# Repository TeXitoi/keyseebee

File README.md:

# KeySeeBee

KeySeeBee is a split ergo keyboard. It is only 2 PCB (so the name)
with (almost) only SMD components on it. It's only a keyboard, no LED,
no display, nothing more than keys and USB.

The firmware is [Keyberon](https://github.com/TeXitoi/keyberon), a
pure rust firmware.

## Features

 * 44 keys, using Cherry MX or Kailh choc switches, only 1U keycaps.
 * USB-C connector on the 2 sides.
 * TRRS cable for connecting the 2 halves (for power and UART communication between the 2 halves).
 * 2 STM32F072 MCU, with hardware USB DFU bootloader and crystal less USB;
 * Only onboard SMD component (except for the switches and TRRS
   connector).
 * [Plate files](cad/) (optional).

## Inspiration

 * [Plaid](https://github.com/hsgw/plaid) for "show the components"
 * [GergoPlex](https://www.gboards.ca/product/gergoplex) for "just a keyboard" and "only a PCB with SMD components"
 * [Lily58](https://github.com/kata0510/Lily58) for the thumb cluster
 * [Kyria](https://blog.splitkb.com/blog/introducing-the-kyria) for
   "don't be affraid of pinky stagger"

## Gallery

### v0.1, build by TeXitoi

### v0.1, build by TeXitoi, Gateron silent clear (MX footprint), 3D printed plate

### v0.2, build by eropleco, with 1.2mm anodized aluminium plate

### v0.3, build by TeXitoi, Gateron silent clear, 3D printed fat plate

## Bill Of Materials

Price is for 5 keyboards including shipping.

|Item                                                                      |Package|Qty|Remarks                                |Price |
|--------------------------------------------------------------------------|-------|--:|---------------------------------------|-----:|
|[Left PCB](pcb/gerbers/)                                                  |       |  1|Ordered at [JLCPCB](https://jlcpcb.com)|      |
|[Right PCB](pcb/gerbers/)                                                 |       |  1|Ordered at [JLCPCB](https://jlcpcb.com)|33.14€|
|[USB-C connector](https://www.aliexpress.com/item/33004501788.html)       |16 pins|  2|                                       | 1.44€|
|[1N4148WS](https://www.aliexpress.com/item/32774043752.html)              |SOD-323| 44|Price is for 1000                      | 2.82€|
|[PJ320A TRRS connector](https://www.aliexpress.com/item/4000661212458.html)|      |  2|                                       | 1.01€|
|[STM32F072CBT6 MCU](https://www.aliexpress.com/item/1005002841528809.html)|LQFP-48|  2|STM32F072C8T6 would also work          | 9.65€|
|[XC6206P332MR regulator](https://www.aliexpress.com/item/33015891307.html)|SOT-23 |  2|Price is for 50                        | 1.93€|
|[SMD switch](https://www.aliexpress.com/item/4000546059630.html)          | 3×6mm |  4|Price is for 100                       | 1.35€|
|[5.1kΩ resistor](https://www.aliexpress.com/item/32865947306.html)        | 0805  |  6|Price is for 100                       |      |
|[1µF capacitor](https://www.aliexpress.com/item/32964553793.html)         | 0805  |  4|Price is for 100                       |      |
|[100nF capacitor](https://www.aliexpress.com/item/32964553793.html)       | 0805  | 10|Price is for 100                       | 3.46€|
|[Bumpers](https://www.aliexpress.com/item/32289191938.html)               | 5×2mm | 10|Price is for 100                       | 1.75€|
|[Cherry MX compatible](https://www.aliexpress.com/item/32836368723.html) or [Kailh Choc](https://www.aliexpress.com/item/1005005883472162.html) switch|5 pins (PCB mount)|44| | |
|1U keycap compatible with the chosen switches                             |       | 44|                                       |      |
|[TRRS cable](https://www.aliexpress.com/item/1005003677396291.html)       |Jack 3.5mm| 1|4 contacts needed                    |      |
|[USB-C cable](https://www.aliexpress.com/item/1005002811739151.html)      |       |  1|USB-2 is enough                        |      |

About 60€ without switches, keycaps and cables for 5 keyboards
(12€/keyboard).

## Compiling and flashing

Install the complete toolchain and utils:

```shell
curl https://sh.rustup.rs -sSf | sh
rustup target add thumbv6m-none-eabi
rustup component add llvm-tools-preview
cargo install cargo-binutils
sudo apt-get install dfu-util
```

Compile:

```shell
cd firmware
cargo objcopy --bin keyseebee --release -- -O binary keyseebee.bin
```

To flash using dfu-util, launch it with:
```shell
dfu-util -w -d 0483:df11 -a 0 -s 0x08000000:leave -D keyseebee.bin
```
Then, put the board in dfu mode by pressing BOOT, pressing and releasing
RESET and releasing BOOT. The upload should began as soon as the
computer detect the board in dfu mode.

The first time, if the write fail, your flash might be protected. To
unprotect:

```shell
dfu-util -d 0483:df11 -a 0 -s 0x08000000:force:unprotect -D keyseebee.bin
```

Ideally both sides needs to be flashed, but for changes that only affect the layout it's strictly not needed as the side connected with the USB cable will determine the layout. In fact, you can have different layouts stored on each half, meaning you can switch back and forth between two layouts by moving the USB cable between the two halves.

## What's the layout

Here is the [empty keyboard-layout-editor](http://www.keyboard-layout-editor.com/##@_name=Keyseebee%3B&@_y:0.35&x:3&sm=cherry&a:7&f:4%3B&=&_x:9%3B&=%3B&@_y:-0.85&x:2%3B&=&_x:1%3B&=&_x:7%3B&=&_x:1%3B&=%3B&@_y:-0.875&x:5%3B&=&_x:5%3B&=%3B&@_y:-0.625&x:1%3B&=&_x:13%3B&=%3B&@_y:-0.8500000000000001%3B&=&_x:15&f:3%3B&=%3B&@_y:-0.8&x:3&f:4%3B&=&_x:9%3B&=%3B&@_y:-0.8500000000000001&x:2%3B&=&_x:1%3B&=&_x:7%3B&=&_x:1%3B&=%3B&@_y:-0.875&x:5%3B&=&_x:5%3B&=%3B&@_y:-0.625&x:1%3B&=&_x:13%3B&=%3B&@_y:-0.8500000000000001%3B&=&_x:15&f:3%3B&=%3B&@_y:-0.7999999999999998&x:3&f:4%3B&=&_x:9%3B&=%3B&@_y:-0.8500000000000001&x:2%3B&=&_x:1%3B&=&_x:7%3B&=&_x:1%3B&=%3B&@_y:-0.875&x:5%3B&=&_x:5%3B&=%3B&@_y:-0.625&x:1%3B&=&_x:13%3B&=%3B&@_y:-0.8500000000000001%3B&=&_x:15&f:3%3B&=%3B&@_y:-0.6499999999999999&x:2.5&f:4%3B&=&_x:10%3B&=%3B&@_rx:4&ry:8.175&y:-4.675&x:-0.5%3B&=%3B&@_y:-0.875&x:0.5%3B&=%3B&@_rx:13&y:-4.675&x:-0.5%3B&=%3B&@_y:-0.875&x:-1.5%3B&=%3B&@_r:30&rx:4&y:-4.825&x:-0.5&f:3%3B&=%3B&@_r:-30&rx:13&y:-4.825&x:-0.5%3B&=) describing the layout.

I use the [ergol layout](https://ergol.org), so this is [the main layer](http://www.keyboard-layout-editor.com/##@_name=keyseebee%20Ergo-l%3B&@_y:0.35&x:3&sm=cherry&f:4%3B&=%0A%0A%C5%93%0A%3E%0A%0A%0AO&_x:9%3B&=%0A%0A%2F_%0A*%0A%0A%0AD%3B&@_y:-0.8500000000000001&x:2%3B&=%0A%0A%C3%A7%0A%3C%0A%0A%0AC&_x:1%3B&=%0A%0A%C3%B4%0A$%0A%0A%0AP&_x:7%3B&=%0A%0A%C2%B5%0A%2F&%0A%0A%0AM&_x:1%3B&=!%0A%E2%91%A0%0A%C2%A8%0A'%3B&@_y:-0.875&x:5%3B&=%0A%0A%0A%25%0A%0A%0AW&_x:5%3B&=%0A%0A%0A%2F@%0A%0A%0AJ%3B&@_y:-0.625&x:1%3B&=%0A%0A%C3%A2%0A%5E%0A%0A%0AQ&_x:13%3B&=%0A%0A%C3%BB%0A%60%0A%0A%0AY%3B&@_y:-0.8500000000000001&a:6%3B&=Tab&_x:15&a:4&f:3%3B&=%7B%0A%5B%3B&@_y:-0.7999999999999998&x:3&f:4%3B&=%0A%0A%C3%A8%0A%29%0A%0A%0AE&_x:9%3B&=%0A%0A%C3%AE%0A-%0A%0A%0AT%3B&@_y:-0.8500000000000001&x:2%3B&=%0A%0A%C3%A9%0A%28%0A%0A%0AS&_x:1%3B&=%0A%0A%C3%AA%0A%7D%0A%0A%0AN&_x:7%3B&=%0A%0A%29%0A+%0A%0A%0AR&_x:1%3B&=%0A%0A%C3%AF%0A%2F%2F%0A%0A%0AI%3B&@_y:-0.875&x:5%3B&=%0A%0A%C3%B1%0A%2F=%0A%0A%0AF&_x:5%3B&=%0A%0A%28%0A%5C%0A%0A%0AL%3B&@_y:-0.625&x:1%3B&=%0A%0A%C3%A0%0A%7B%0A%0A%0AA&_x:13%3B&=%0A%0A%C3%B9%0A%22%0A%0A%0AU%3B&@_y:-0.8500000000000001%3B&=%7D%0A%5D&_x:15&f:3%3B&=%22%0A'%3B&@_y:-0.7999999999999998&x:3&f:4%3B&=%3F%0A-%0A%E2%80%91%0A%5D&_x:9%3B&=%0A%0A%CE%B1%0A%2F%3B%0A%0A%0AG%3B&@_y:-0.8500000000000001&x:2%3B&=%0A%0A%C3%9F%0A%5B%0A%0A%0AX&_x:1%3B&=%0A%0A%E2%80%93%0A%2F_%0A%0A%0AV&_x:7%3B&=%0A%0A%0A!%0A%0A%0AH&_x:1%3B&=%2F%3B%0A,%0A%C2%B7%0A%2F:%3B&@_y:-0.875&x:5%3B&=%0A%0A%E2%80%94%0A%23%0A%0A%0AB&_x:5%3B&=%2F:%0A.%0A%E2%80%A6%0A%7C%3B&@_y:-0.625&x:1%3B&=%0A%0A%C3%A6%0A~%0A%0A%0AZ&_x:13%3B&=%0A%0A%C5%AD%0A%3F%0A%0A%0AK%3B&@_y:-0.8500000000000001%3B&=+%0A%2F=&_x:15&f:3%3B&=%7C%0A%5C%3B&@_y:-0.6500000000000004&x:2.5&a:6&f:4%3B&=GUI&_x:10%3B&=%E2%87%A7%20+%20AltGr%3B&@_rx:4&ry:8.175&y:-4.675000000000001&x:-0.5%3B&=Alt%3B&@_y:-0.875&x:0.5&a:0%3B&=nbsp%0A%E2%90%A3%0A%E2%80%99%0A%E2%90%A3%0Alayer%201%3B&@_rx:13&y:-4.675000000000001&x:-0.5&a:6%3B&=AltGr%3B&@_y:-0.875&x:-1.5&a:7%3B&=Layer%202%3B&@_r:30&rx:4&y:-4.825000000000001&x:-0.5&a:6&f:3%3B&=Ctrl%3B&@_r:-30&rx:13&y:-4.825000000000001&x:-0.5%3B&=%E2%87%A7) when I type.

The [layer 1](http://www.keyboard-layout-editor.com/##@_name=Keyseebee%20layer%201%3B&@_y:0.35&x:3&sm=cherry&a:7&f:4%3B&=Scroll%20Lock&_x:9%3B&=Del.%3B&@_y:-0.85&x:2%3B&=Caps%20Lock&_x:1%3B&=Print%20Scr.&_x:7%3B&=%E2%8C%AB&_x:1%3B&=Insert%3B&@_y:-0.875&x:5%3B&=%E2%87%A7%20+%20Tab&_x:5%3B&=%3B&@_y:-0.625&x:1%3B&=Break&_x:13%3B&=%3B&@_y:-0.8500000000000001%3B&=&_x:15&f:3%3B&=%3B&@_y:-0.8&x:3&f:4%3B&=Esc.%0A%0A%0A%0ACtrl&_x:9%3B&=%E2%96%BC%3B&@_y:-0.8500000000000001&x:2%3B&=Alt&_x:1%3B&=%E2%87%A7&_x:7%3B&=%E2%97%84&_x:1%3B&=%E2%96%B2%3B&@_y:-0.875&x:5%3B&=Tab&_x:5%3B&=%3B&@_y:-0.625&x:1%3B&=GUI&_x:13%3B&=%E2%96%BA%3B&@_y:-0.8500000000000001%3B&=&_x:15&f:3%3B&=%3B&@_y:-0.7999999999999998&x:3&f:4%3B&=Copy&_x:9%3B&=%E2%87%9F%3B&@_y:-0.8500000000000001&x:2%3B&=Cut&_x:1%3B&=Paste&_x:7%3B&=%E2%87%B1&_x:1%3B&=%E2%87%9E%3B&@_y:-0.875&x:5%3B&=&_x:5%3B&=%E2%8F%8E%3B&@_y:-0.625&x:1%3B&=Undo&_x:13%3B&=%E2%87%B2%3B&@_y:-0.8500000000000001%3B&=&_x:15&f:3%3B&=%3B&@_y:-0.6499999999999999&x:2.5&f:4%3B&=&_x:10%3B&=%3B&@_rx:4&ry:8.175&y:-4.675&x:-0.5%3B&=%3B&@_y:-0.875&x:0.5&g:true%3B&=%3B&@_rx:13&y:-4.675&x:-0.5&g:false%3B&=%3B&@_y:-0.875&x:-1.5%3B&=Layer%203%3B&@_r:30&rx:4&y:-4.825&x:-0.5&f:3%3B&=%3B&@_r:-30&rx:13&y:-4.825&x:-0.5&f:4%3B&=) is activated by holding `space`.

The [layer 2](http://www.keyboard-layout-editor.com/##@_name=keyseebee%20layer%203%3B&@_y:0.35&x:3&sm=cherry&a:7&f:4%3B&=%C2%BB&_x:9%3B&=%3B&@_y:-0.85&x:2%3B&=%C2%AB&_x:1%3B&=nbsp&_x:7%3B&=&_x:1%3B&=%E2%91%A0%3B&@_y:-0.875&x:5%3B&=&_x:5%3B&=%3B&@_y:-0.625&x:1%3B&=%E2%82%AC&_x:13%3B&=%3B&@_y:-0.8500000000000001%3B&=&_x:15&f:3%3B&=%3B&@_y:-0.8&x:3&f:4%3B&=3&_x:9%3B&=8%3B&@_y:-0.8500000000000001&x:2%3B&=2&_x:1%3B&=4&_x:7%3B&=7&_x:1%3B&=9%3B&@_y:-0.875&x:5%3B&=5&_x:5%3B&=6%3B&@_y:-0.625&x:1%3B&=1&_x:13%3B&=0%3B&@_y:-0.8500000000000001%3B&=%60&_x:15&f:3%3B&=%2F%2F%3B&@_y:-0.7999999999999998&x:3&f:4%3B&=%2F:&_x:9%3B&=-%3B&@_y:-0.8500000000000001&x:2%3B&=nbsp&_x:1%3B&=,&_x:7%3B&=+&_x:1%3B&=%2F%2F%3B&@_y:-0.875&x:5%3B&=%2F=&_x:5%3B&=.%3B&@_y:-0.625&x:1%3B&=&_x:13%3B&=*%3B&@_y:-0.8500000000000001%3B&=&_x:15&f:3%3B&=%3B&@_y:-0.6499999999999999&x:2.5&a:6&f:4%3B&=GUI&_x:10&a:7%3B&=%3B&@_rx:4&ry:8.175&y:-4.675&x:-0.5&a:6%3B&=Alt%3B&@_y:-0.875&x:0.5&a:7%3B&=Ctrl+%E2%90%A3%3B&@_rx:13&y:-4.675&x:-0.5%3B&=AltGr%3B&@_y:-0.875&x:-1.5&g:true%3B&=%3B&@_r:30&rx:4&y:-4.825&x:-0.5&g:false&a:6&f:3%3B&=Ctrl%3B&@_r:-30&rx:13&y:-4.825&x:-0.5%3B&=%E2%87%A7) is activated by holding `Layer 2`.

The [layer 3](http://www.keyboard-layout-editor.com/##@_name=Keyseebee%20layer%203%3B&@_y:0.35&x:3&sm=cherry&a:7&f:4%3B&=F3&_x:9%3B&=F8%3B&@_y:-0.85&x:2%3B&=F2&_x:1%3B&=F4&_x:7%3B&=F7&_x:1%3B&=F9%3B&@_y:-0.875&x:5%3B&=F5&_x:5%3B&=F6%3B&@_y:-0.625&x:1%3B&=F1&_x:13%3B&=F10%3B&@_y:-0.8500000000000001%3B&=&_x:15&f:3%3B&=%3B&@_y:-0.8&x:3&f:4%3B&=Ctrl&_x:9%3B&=Ctrl%3B&@_y:-0.8500000000000001&x:2%3B&=Alt&_x:1%3B&=%E2%87%A7&_x:7%3B&=%E2%87%A7&_x:1%3B&=Alt%3B&@_y:-0.875&x:5%3B&=&_x:5%3B&=%3B&@_y:-0.625&x:1%3B&=GUI&_x:13%3B&=GUI%3B&@_y:-0.8500000000000001%3B&=&_x:15&f:3%3B&=%3B&@_y:-0.7999999999999998&x:3&f:4%3B&=&_x:9%3B&=%3B&@_y:-0.8500000000000001&x:2%3B&=F12&_x:1%3B&=&_x:7%3B&=&_x:1%3B&=%3B&@_y:-0.875&x:5%3B&=&_x:5%3B&=%3B&@_y:-0.625&x:1%3B&=F11&_x:13%3B&=%3B&@_y:-0.8500000000000001%3B&=&_x:15&f:3%3B&=%3B&@_y:-0.6499999999999999&x:2.5&f:4%3B&=Boot%20DFU&_x:10%3B&=%3B&@_rx:4&ry:8.175&y:-4.675&x:-0.5%3B&=%3B&@_y:-0.875&x:0.5&g:true%3B&=%3B&@_rx:13&y:-4.675&x:-0.5&g:false%3B&=%3B&@_y:-0.875&x:-1.5&g:true%3B&=%3B&@_r:30&rx:4&y:-4.825&x:-0.5&g:false&f:3%3B&=%3B&@_r:-30&rx:13&y:-4.825&x:-0.5&f:4%3B&=)
is activaded by holding `space` then `Layer 2`.

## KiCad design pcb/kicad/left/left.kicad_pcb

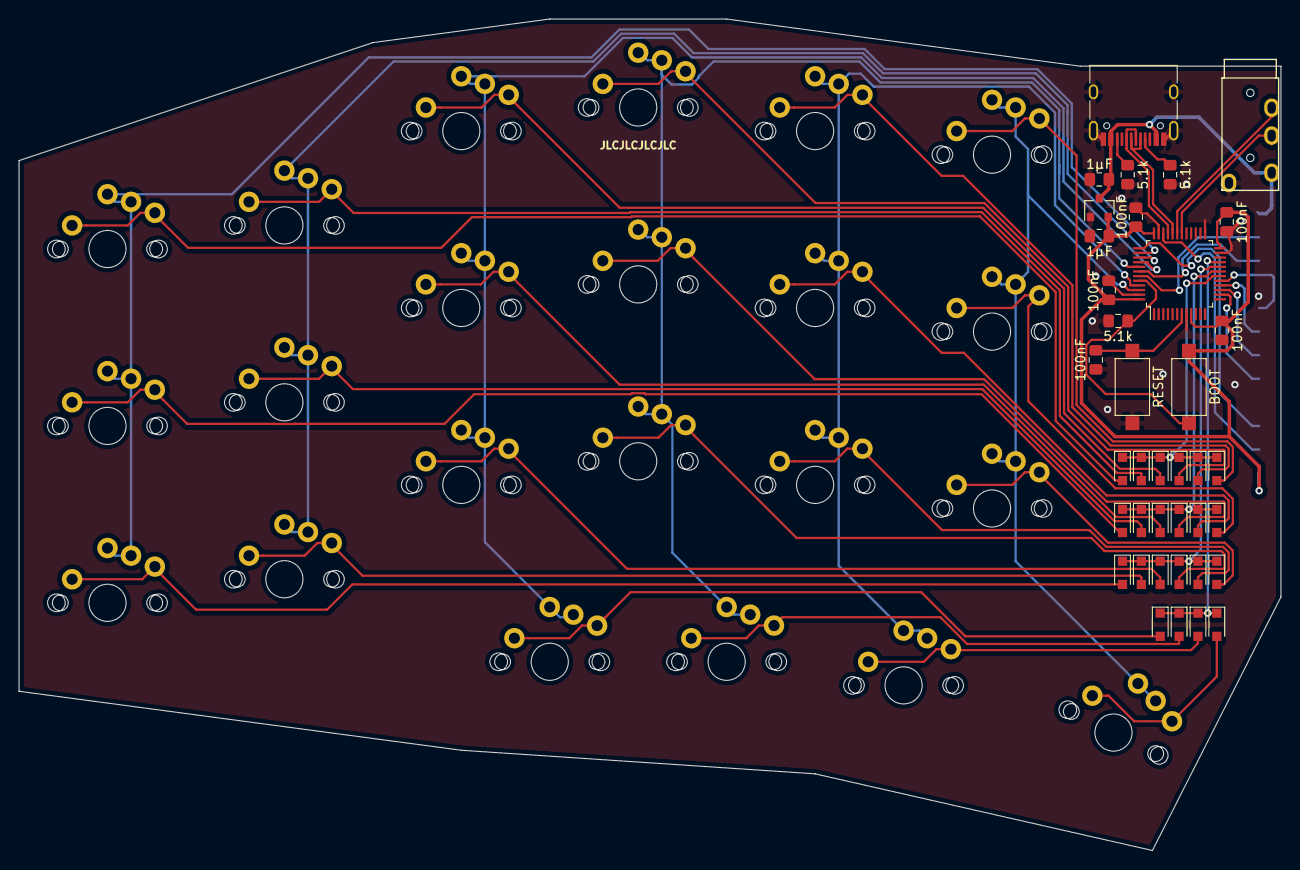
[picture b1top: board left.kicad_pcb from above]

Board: 2 copper layers, 135.9 x 89.5 mm, 61 parts (1 on the bottom side), 51 nets.

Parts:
C1, C2, C3, C4, C5: 100nF; C_0805_2012Metric_Pad1.15x1.40mm_HandSolder
C6, C7: 1µF; C_0805_2012Metric_Pad1.15x1.40mm_HandSolder
D5, D6, D7, D9, D10, D11, D12, D14, D15, D16, D17, D19, D20, D21, D23, D24, D25, D26, D33, D34, D35, D36: 1N4148WS; D_SOD-323_HandSoldering
J1: USB_C_Receptacle_USB2.0; USB_C_Receptacle_HRO_TYPE-C-31-M-12
J2: AudioJack4; TRRS-PJ-320A-no-Fmask
J3: Conn_01x12_Male; Harwin_M20-89012xx_1x12_P2.54mm_Horizontal
R1, R6, R7: 5.1k; R_0805_2012Metric_Pad1.15x1.40mm_HandSolder
SW1: BOOT; SW_SPST_CK_RS282G05A3
SW2: RESET; SW_SPST_CK_RS282G05A3
SW3, SW4, SW5, SW7, SW8, SW9, SW10, SW12, SW13, SW14, SW15, SW17, SW18, SW19, SW21, SW22, SW23, SW24, SW31, SW32, SW33, SW34: SW_Push; CherryMX_Choc_1u
U1: STM32; LQFP-48_7x7mm_P0.5mm
U2: LDO; SOT-23

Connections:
3.3V: C2.2, C3.2, C4.2, C5.2, C6.2, J3.1, SW1.2, U1.9, U1.24, U1.36, U1.48, U2.2
5V: C7.2, J1.A4, J1.A9, J1.B4, J1.B9, J2.2, J3.12, U2.3
COL1: SW3.2, SW4.2, SW5.2, U1.38
COL2: SW17.2, SW18.2, SW19.2, U1.39
COL3: SW7.2, SW8.2, SW9.2, SW10.2, U1.40
COL4: SW21.2, SW22.2, SW23.2, SW24.2, U1.41
COL5: SW31.2, SW32.2, SW33.2, SW34.2, U1.45
COL6: SW12.2, SW13.2, SW14.2, SW15.2, U1.46
D+: J1.A6, J1.B6, U1.33
D-: J1.A7, J1.B7, U1.32
GND: C1.1, C2.1, C3.1, C4.1, C5.1, C6.1, C7.1, J1.A1, J1.A12, J1.B1, J1.B12, J1.S1, J2.1, J3.4, J3.9, R1.2, R6.2, R7.2, SW2.1, U1.8, U1.23, U1.25, U1.35, U1.47, U2.1
unnamed: C1.2, SW2.2, U1.7
unnamed: D5.2, SW3.1
unnamed: D6.2, SW4.1
unnamed: D7.2, SW5.1
unnamed: D9.2, SW7.1
unnamed: D10.2, SW8.1
unnamed: D11.2, SW9.1
unnamed: D12.2, SW10.1
unnamed: D14.2, SW12.1
unnamed: D15.2, SW13.1
unnamed: D16.2, SW14.1
unnamed: D17.2, SW15.1
unnamed: D19.2, SW17.1
unnamed: D20.2, SW18.1
unnamed: D21.2, SW19.1
unnamed: D23.2, SW21.1
unnamed: D24.2, SW22.1
unnamed: D25.2, SW23.1
unnamed: D26.2, SW24.1
unnamed: D33.2, SW31.1
unnamed: D34.2, SW32.1
unnamed: D35.2, SW33.1
unnamed: D36.2, SW34.1
unnamed: J1.A5, R7.1
unnamed: J1.B5, R6.1
unnamed: R1.1, SW1.1, U1.44
PA4: J3.5, U1.14
PA5: J3.6, U1.15
PA6: J3.7, U1.16
PA7: J3.8, U1.17
PB6: J3.10, U1.42
PB7: J3.11, U1.43
ROW1: D5.1, D9.1, D14.1, D19.1, D23.1, D33.1, U1.18
ROW2: D6.1, D10.1, D15.1, D20.1, D24.1, D34.1, U1.19
ROW3: D7.1, D11.1, D16.1, D21.1, D25.1, D35.1, U1.20
ROW4: D12.1, D17.1, D26.1, D36.1, U1.21
RX: J2.4, U1.31
SWDCLK: J3.3, U1.37
SWDIO: J3.2, U1.34
TX: J2.3, U1.30

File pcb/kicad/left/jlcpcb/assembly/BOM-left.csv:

Comment,Designator,Footprint,LCSC
USB_C_Receptacle_USB2.0,J1,USB_C_Receptacle_HRO_TYPE-C-31-M-12,C136423
1N4148WS,"D10,D11,D12,D14,D15,D16,D17,D19,D20,D21,D23,D24,D25,D26,D33,D34,D35,D36,D5,D6,D7,D9",D_SOD-323_HandSoldering,C2128
5.1k,"R1,R6,R7",R_0805_2012Metric_Pad1.15x1.40mm_HandSolder,C27834
100nF,"C1,C2,C3,C4,C5",C_0805_2012Metric_Pad1.15x1.40mm_HandSolder,C28233
1µF,"C6,C7",C_0805_2012Metric_Pad1.15x1.40mm_HandSolder,C28323
AudioJack4,J2,TRRS-PJ-320A-no-Fmask,C2884926
LDO,U2,SOT-23,C5446
BOOT,"SW1,SW2",SW_SPST_CK_RS282G05A3,C720381
STM32,U1,LQFP-48_7x7mm_P0.5mm,C80488

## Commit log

2020-07-04 Import left pcb
2020-07-05 right advances
2020-07-06 right: placement + 3.3V
2020-07-06 more trace
2020-07-07 right: rows routed
2020-07-07 Right routed
2020-07-30 fix diode bug on right
2020-07-30 right: small tweeks
2020-07-30 right: silk
2020-07-30 left: correct diode bug
2020-07-30 left: change switch footprint
2020-07-30 left: silk
2020-07-30 big tracks for power
2020-07-30 small tweaks
2020-08-02 smaller text
2020-08-02 custom switch footprint
2020-08-02 gerber conf
2020-08-02 order number placeholder for JLPCB
2020-08-02 generated gerber for v0.1
2020-08-02 first compiling firmware
2020-08-04 some cleanups
2020-08-05 handle side transposition
2020-08-18 Compiling and flashing in the README
2020-08-18 Fix LDO
2020-08-18 Fix diode orientation
2020-08-18 update gerber changelog
2020-08-19 Blind implementation of serial communication
2020-08-19 remove unwrap
2020-08-19 cargo clippy
2020-08-20 fix transpose
2020-08-28 more functionnal firmware for serial communication (but still doesn't work)
2020-08-28 Higher priority for RX, better but still losing events
2020-08-28 functional keyboard!
2020-08-30 Images and updates of the md files
2020-09-01 fix race condition
2020-09-01 fix typo in README.md
2020-09-05 v0.2
2020-09-05 cargo update
2020-09-12 BOM corrections
2020-09-12 BOM typo cleaning
2020-09-12 better BOM
2020-09-25 Correct MCU package in BOM
2020-10-03 Change TRRS Aliexpress link
2020-11-02 Plate, without extreme thumb key
2020-11-03 complete plate
2020-11-03 Corrected plates
2020-11-03 Document the cad directory
2020-11-03 Report right thumb offset
2020-11-03 Correct version numbering
2020-11-04 Add note about which side needs flashing
2020-11-05 left side of choc version.
2020-11-06 Comment the cad/plate.scad file
2020-11-08 right side.
2020-11-08 made the right side's routing more similar to the left side's.
2020-11-08 missed some routes.
2020-11-08 nine mm difference.
2020-11-19 Add eropleco's build
2020-12-02 Corrections on the PCB
2020-12-03 Add photo
2020-12-03 Update link for MCU
    fixes #7
2020-12-11 keyberon master + layout tweeks
2020-12-15 add keyboard-layout-editor export
2020-12-15 Small tweeks on kle layer 0
2020-12-28 improve keymap
2021-07-27 Update to latest keyberon master
2021-08-12 fat MX plate
2021-08-12 tweeks
2021-08-12 cutting pattern
2021-08-13 Add v0.3 images and infos
2021-08-13 Correction on cutting pattern files
2021-08-19 fix typo
2021-08-23 Update aliexpress links
2021-08-27 Correct layer 1 in README.md
2021-08-27 Cleanup a bit layer 2 on README.md
2021-08-27 Small layout tweeks
2021-08-29 Document layer 3 in README.md
2021-09-03 More parallel usb trace on left
2021-10-18 update to latest keyberon
2021-10-18 indentation
2021-10-18 move the layout in its file
2021-10-18 small refactor + bootloader (not reliable)
2021-12-26 Some try at STM assembly (clearly not yet ready)
2022-01-13 Small changes for left manufactured SMT
2022-04-12 layout tweeks
2022-04-13 cargo update + layout macro
2022-04-14 update everything, especially rtic to v1
2022-04-14 Finish migration to rtic
2022-06-13 jlcpcb smt and kicad 6
2022-07-17 More JLCPCB SMT changes
2023-11-03 cargo update (except keyberon)
2023-11-03 update keyberon
2024-01-23 layout small tweeks
2024-02-26 nav for ergo-l
2024-03-25 5×3 layout
2024-04-17 STAB and 6th column back
2024-04-18 More lisible numrow
2024-04-19 Ergo-l layer
2024-04-19 Layer 2 update
2024-04-19 Update layer 3 in README
2024-04-19 Update layer 3
2024-04-19 Correct layouts
2024-05-22 Change num layer for NBSP
2024-05-22 Layout formatting
2024-05-22 shifted numbers are back
2024-05-27 Small tweeks
2024-05-27 working software goto bootloader
2024-05-30 simplify goto bootloader
2024-05-30 remove warnings
2024-05-30 fix goto bootloader for when reset inside bootloader
